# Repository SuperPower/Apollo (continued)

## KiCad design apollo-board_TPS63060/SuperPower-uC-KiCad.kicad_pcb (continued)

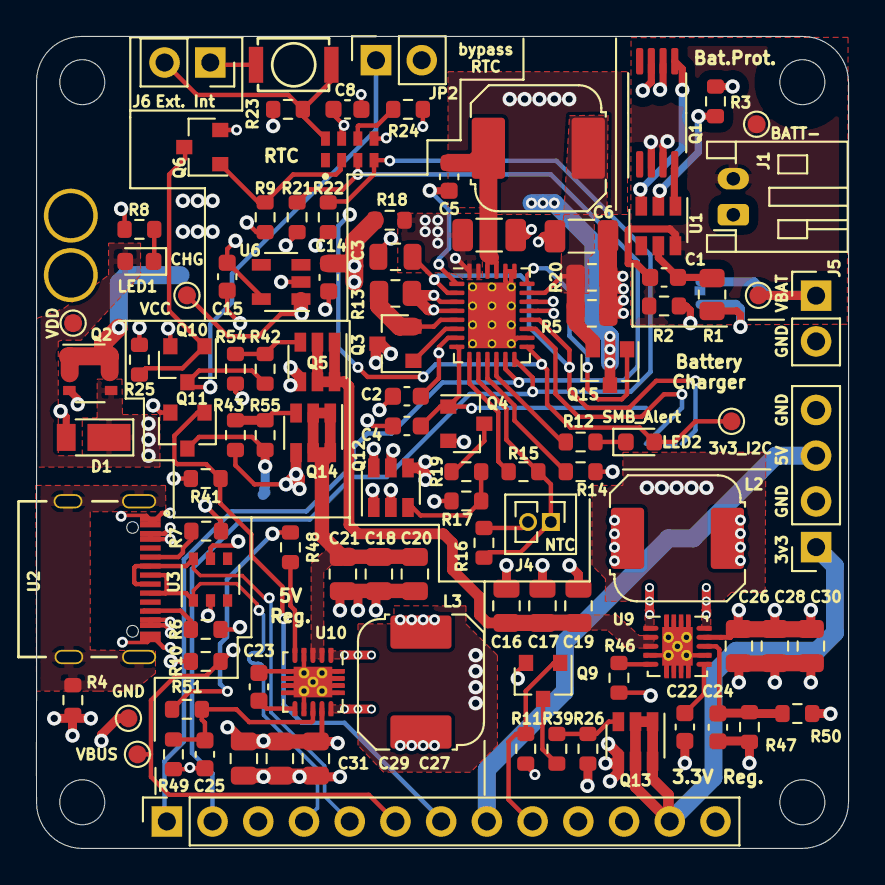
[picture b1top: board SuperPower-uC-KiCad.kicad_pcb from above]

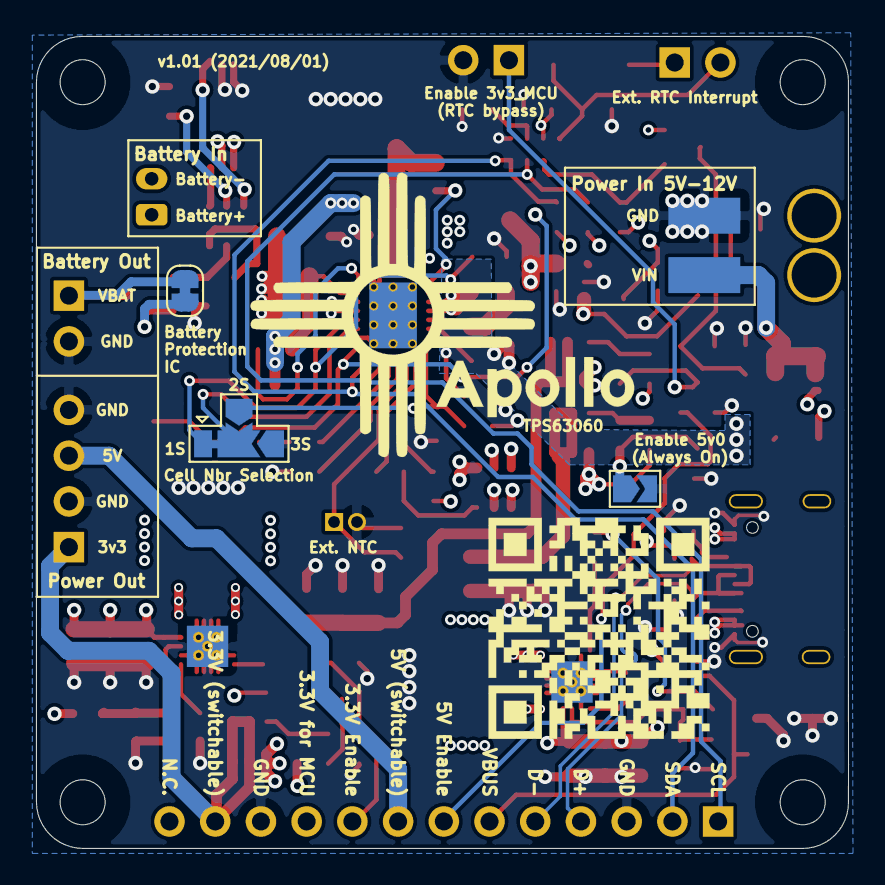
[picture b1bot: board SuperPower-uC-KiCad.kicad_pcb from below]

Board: 4 copper layers, 45.1 x 45.1 mm, 114 parts (4 on the bottom side), 65 nets.

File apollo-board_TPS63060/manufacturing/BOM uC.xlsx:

Item | Qty | Reference(s) | Value | Footprint | Datasheet | Package | DNP
1 | 2 | C1, C2 | CC0603JRX7R9BB104 | Capacitor_SMD:C_0603_1608Metric | https://www.yageo.com/upload/media/product/productsearch/dat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 | 0603
2 | 1 | C3 | TMK212AB7475KG-T | Capacitor_SMD:C_0805_2012Metric | https://eu.mouser.com/datasheet/2/396/mlcc02_e-1307760.pdf | 0805
3 | 1 | C4 | CL10B105KO8NNNC | Capacitor_SMD:C_0603_1608Metric |  | 0603
4 | 1 | C5 | CL10B223KB8NNNC | Capacitor_SMD:C_0603_1608Metric |  | 0603
5 | 2 | C6, C7 | CL31B106KAHNNNE | Capacitor_SMD:C_1206_3216Metric | https://eu.mouser.com/datasheet/2/585/MLCC-1837944.pdf | 1206
6 | 1 | C8 | 0.1µF | Capacitor_SMD:C_0603_1608Metric | ~ | 0603
7 | 2 | C14, C15 | 2.2μF | Capacitor_SMD:C_0603_1608Metric | ~ | 0603
8 | 6 | C16, C17, C18, C19, C20, C21 | CL21A106KAYNNNE | Capacitor_SMD:C_0805_2012Metric | https://www.mouser.fr/datasheet/2/585/MLCC-1837944.pdf | 0805
9 | 2 | C22, C23 | CL10B104KB8NNNC | Capacitor_SMD:C_0603_1608Metric | https://www.mouser.fr/datasheet/2/585/MLCC-1837944.pdf | 0603
10 | 2 | C24, C25 | CC0603JRNPO9BN100 | Capacitor_SMD:C_0603_1608Metric | https://www.mouser.fr/datasheet/2/447/yageo_yago_s_a00092516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 | 0603
11 | 6 | C26, C27, C28, C29, C30, C31 | CL21A226MAQNNNE | Capacitor_SMD:C_0805_2012Metric | https://www.mouser.fr/datasheet/2/585/MLCC-1837944.pdf | 0805
12 | 1 | D1 | DFLS230L | Diode_SMD:D_PowerDI-123 | https://www.diodes.com/assets/Datasheets/ds30515.pdf | PowerDI-123-2
13 | 4 | H1, H2, H3, H4 | MountingHole | MountingHole:MountingHole_2.5mm | ~ |  | DNP
14 | 1 | J1 | JST_PH_S2B_thru | Connector_JST:JST_PH_S2B-PH-K_1x02_P2.00mm_Horizontal | http://www.jst-mfg.com/product/pdf/eng/ePH.pdf | PH Right Angle Thru 2pins
15 | 1 | J3 | Conn_01x02_Male | ext_input:ext_input_pads | ~ |  | DNP
16 | 1 | J4 | DNP/JST_ZH_S2B_thru | Connector_PinHeader_1.27mm:PinHeader_1x02_P1.27mm_Vertical | http://www.jst-mfg.com/product/pdf/eng/eZH.pdf | ZH Right Angle Thru 2pins | DNP
17 | 1 | J5 | DNP/JST_XH_S2B_thru | Connector_PinHeader_2.54mm:PinHeader_1x02_P2.54mm_Vertical | http://www.jst-mfg.com/product/pdf/eng/eXH.pdf | XH Right Angle Thru 2pins | DNP
18 | 1 | J6 | Conn_01x02_Male | Connector_PinSocket_2.54mm:PinSocket_1x02_P2.54mm_Vertical | ~ |  | DNP
19 | 1 | J10 | Conn_01x13_Male | Connector_PinSocket_2.54mm:PinSocket_1x13_P2.54mm_Vertical | ~ |  | DNP
20 | 1 | J11 | Conn_01x04_Male | Connector_PinSocket_2.54mm:PinSocket_1x04_P2.54mm_Vertical | ~ |  | DNP
21 | 1 | JP1 | SolderJumper_4_Bridged_1C | SOLDERJUMPER_4_BRIDGED_1C:SolderJumper-4_P2.0mm_Bridged1C_TrianglePad1.0x1.5mm_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 | ~ |  | DNP
22 | 1 | JP2 | Jumper_NC_Small | Connector_PinSocket_2.54mm:PinSocket_1x02_P2.54mm_Vertical | ~ |  | DNP
23 | 1 | JP3 | Jumper_NC_Small | Jumper:SolderJumper-2_P1.3mm_Open_TrianglePad1.0x1.5mm | ~ |  | DNP
24 | 1 | L1 | SPM6530T-4R7M | SPM6530T-4R7M:L_TDK_SPM6530T | https://product.tdk.com/info/en/catalog/datasheets/inductor_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 | 6,5x7,1x3,0mm
25 | 2 | L2, L3 | SPM6530T-1R5M | SPM6530T-1R5M:L_TDK_SPM6530T | https://product.tdk.com/info/en/catalog/datasheets/inductor_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 | 6,5x7,1x3,0mm
26 | 1 | LED1 | 150060VS75000_0603 | LED_SMD:LED_0603_1608Metric | https://www.we-online.com/catalog/datasheet/150060VS75000.pdf | 0603
27 | 1 | LED2 | 150060YS75000_0603 | LED_SMD:LED_0603_1608Metric | https://www.we-online.com/catalog/datasheet/150060YS75000.pdf | 0603 | DNP
28 | 1 | Q1 | DMN2019UTS | Package_SO:TSSOP-8_4.4x3mm_P0.65mm | https://www.diodes.com/assets/Datasheets/DMN2019UTS.pdf | TSSOP-8
29 | 1 | Q2 | Si3421DV | Package_SO:TSOP-6_1.65x3.05mm_P0.95mm | https://www.diodes.com/assets/Datasheets/DMP2035UVT.pdf | TSOP6
30 | 2 | Q3, Q15 | DMN3023L | Package_TO_SOT_SMD:SOT-23 | ~
31 | 4 | Q4, Q9, Q10, Q11 | 2N7002A | Package_TO_SOT_SMD:SOT-23 | https://www.diodes.com/assets/Datasheets/ds31360.pdf | SOT23-3
32 | 4 | Q5, Q12, Q13, Q14 | DMP2035UVT | Package_TO_SOT_SMD:SOT-23-6 | https://www.diodes.com/assets/Datasheets/DMP2035UVT.pdf | TSOT26
33 | 1 | Q6 | BSS84-7-F | Package_TO_SOT_SMD:SOT-23 | https://www.diodes.com/assets/Datasheets/ds30149.pdf | SOT23-3
34 | 1 | R1 | ERJ-P06F4700V | Resistor_SMD:R_0805_2012Metric | https://industrial.panasonic.com/cdbs/www-data/pdf/RDO0000/A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 | 0805
35 | 2 | R2, R18 | DNP/0 | Resistor_SMD:R_0603_1608Metric | ~ | 0603 | DNP
36 | 1 | R3 | 2.7k | Resistor_SMD:R_0603_1608Metric | ~ | 0603
37 | 1 | R4 | DNP/0 | Resistor_SMD:R_0603_1608Metric | ~ | 0603 | DNP
38 | 2 | R6, R7 | 5.1k | Resistor_SMD:R_0603_1608Metric | ~ | 0603
39 | 1 | R8 | 2.2k | Resistor_SMD:R_0603_1608Metric | ~ | 0603
40 | 4 | R9, R39, R54, R55 | 390k | Resistor_SMD:R_0603_1608Metric | ~ | 0603
41 | 1 | R10 | 12k | Resistor_SMD:R_0603_1608Metric | ~ | 0603
42 | 9 | R11, R25, R26, R41, R42, R43, R46, R48, R51 | 1M | Resistor_SMD:R_0603_1608Metric | ~ | 0603
43 | 1 | R12 | 2.2k | Resistor_SMD:R_0603_1608Metric | ~ | 0603 | DNP
44 | 2 | R13, R20 | RL0805FR-7W0R068L | Resistor_SMD:R_0805_2012Metric | https://www.yageo.com/upload/media/product/productsearch/dat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 | 0805
45 | 1 | R14 | 63.4k | Resistor_SMD:R_0603_1608Metric | ~ | 0603
46 | 2 | R15, R16 | 10k | Resistor_SMD:R_0603_1608Metric | ~ | 0603
47 | 1 | R17 | 1M | Resistor_SMD:R_0603_1608Metric | ~ | 0603
48 | 1 | R19 | 390k | Resistor_SMD:R_0603_1608Metric | ~ | 0603
49 | 2 | R21, R22 | 4.7k | Resistor_SMD:R_0603_1608Metric | ~ | 0603
50 | 1 | R23 | 100k | Resistor_SMD:R_0603_1608Metric | ~ | 0603
51 | 1 | R24 | 10k | Resistor_SMD:R_0603_1608Metric | ~ | 0603
52 | 1 | R47 | 100k | Resistor_SMD:R_0603_1608Metric | ~ | 0603
53 | 1 | R49 | 110k | Resistor_SMD:R_0603_1608Metric | ~ | 0603
54 | 1 | R50 | 560k | Resistor_SMD:R_0603_1608Metric | ~ | 0603
55 | 1 | SW1 | SKRKAEE020 | SKRKAEE020:SKRKAEE020
56 | 1 | U1 | AP9101CK6-AYTRG1 | Package_TO_SOT_SMD:SOT-23-6 | https://www.diodes.com/assets/Datasheets/AP9101C.pdf | SOT23-6
57 | 1 | U2 | USB-C | usb_c:usb-c-usb4105 | https://gct.co/files/drawings/usb4105.pdf
58 | 1 | U3 | IP4220CZ6 | Package_SO:TSOP-6_1.65x3.05mm_P0.95mm | https://assets.nexperia.com/documents/data-sheet/IP4220CZ6.pdf
59 | 1 | U4 | LTC4162EUFD-LAD | Package_DFN_QFN:QFN-28-1EP_4x5mm_P0.5mm_EP2.65x3.65mm_ThermalVias | https://www.analog.com/media/en/technical-documentation/data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 | QFN-28 (2.65x3.65mm)
60 | 1 | U5 | RV-3028-C7 | RV-3028-C7:IC_RV-3028-C7 | https://www.microcrystal.com/fileadmin/Media/Products/RTC/Da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
61 | 1 | U8 | TPS70933DRVT | Package_TO_SOT_SMD:SOT-23-6 | https://www.ti.com/lit/gpn/tps709
62 | 2 | U9, U10 | TPS63060 | TPS63060:Texas_S-PWSON-N10_ThermalVias_NSM_vias_bottom | http://www.ti.com/lit/ds/symlink/tps63060.pdf

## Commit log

2021-02-21 Move Repo and reduce project files to only contain the Apollo Board
2021-02-22 Replace TPS63070 by TPS63060 (U9)
    - Schematic Only
    - Update Netlist
    Rem. : 18650 bat. holder + DC Power Jack + TP (x7) are added while update from schematic process.
2021-02-22 Remove unused parts at schematic level.
    + solve schematic DRC issues
2021-02-22 Place and route U9 (TPS63060)
    + re-place other parts
    + re-design planes shapes
    + display some silkscreen Ref. Des
    + misc. improvements.
2021-02-23 Add TPS63060 component files
    + 3D package
2021-02-24 Update 22µF 0805 & 100nF 0603 capacitors
    around TPS63060
2021-02-24 Update 10µF 0805 capacitors
    Around TPS63060
2021-02-24 Update 10pF 0603 capacitor
    around TPS63060
2021-02-27 Place and route the 2nd TPS63060 (+5V)
2021-02-27 Update 22µF 0805 and 10pF 0603 capacitors
    + Silk Ref. Des.
2021-02-27 Update 10µF 0805 and 100nF 0603 capacitors
    + silk Ref. Des.
    Rem. : Apollo Logo and name on Silkscreen Bottom seem to be lost.
2021-02-28 Update +5V Buck-Boost Feedback resistor values
2021-02-28 Use a new footprint for TPS63060 chips
    Remove Bottom Soldermask on vias
2021-02-28 Improve USB Data diff. Pair length.
2021-02-28 Update Buck-Boost Feedback Resistor values
    - Use common values + bridge divider iq >3µA
    - Misc. Routing : increase one track width from 0.25 to 0.28mm (+5V Output)
2021-02-28 Update USB-C receptacle symbol fields
    Add Mfr Name & ref., DataSheet + Alternative Equivalent Part
2021-02-28 Re-Add "Apollo Logo" on Silkscreen bottom Layer
2021-02-28 Update "RTC Bypass" text position
    + Add "-A" extension pour TPS63060 variant
2021-03-01 Update Silkscreen board informations
    + Add a 12x12mm Text QR-Code
2021-03-03 Replace Text Data QR Code by Web Link QR Code
    https://superpower.github.io/docs/uc/prod/apv100/
2021-03-03 Replace QR-Code by 5x5mm size (x2)
    Web Link + Text Datas
2021-03-08 Generated manufacturing files (deleted wrong gerbers)
2021-03-09 Update TPS63060 chips footprint
    Removing "Solder Mask Openings" between EPad pins for each row
2021-03-09 Update QR-Code Web Link Size
    replace 5x5mm by 12x12mm
2021-04-06 Fixed PNP file
2021-06-13 Recreate TPS709 symbol to and set footprint to SOT23-5
2021-06-13 Connected VIN to I2C_REG
2021-06-13 Swapped Q3 and Q15 Symbol + Footprint
2021-06-13 Moved C3 closer to the LTC
2021-07-19 Remove SMBALERT wire
    between LTC4162-L chip (pin12) and the 2.54mm pitch 13pin connector (pin13). It will allow to use this pin for "one wire" RGB LED (RGB LED Out)
2021-07-19 Update SMBALERT LED (LED2) and resistor (R12) to DNP (Do Not Populate)
2021-07-19 Add a Solder Jumper (shorted by default) between Vbat+ and R1 (AP9101)
2021-07-19 Clean "Battery Protection IC" schematic
2021-07-19 Update "Main Schematic" text
2021-07-19 Update and clean "charger" sheet + add "Vcc" test point
2021-07-19 Rename some power signal on Schematic to improve readability.
    + Misc. updates
2021-07-19 Improve Power tracks width on Bottom Layer
2021-07-19 Improve Power Tracks width and Vias on Top Layer (+3.3V regulator)
2021-07-19 Improve PowerTracks width and Vias on Top Layer (+5.0V)
    + Flip JP3
2021-07-19 Improve Power Tracks width and Vias on Top Layer (+3.3V)
2021-07-19 Improve Tracks width and vias around LTC4162-L
2021-07-19 Improve Tracks width and Vias around LTC4162-L (Q3)
2021-07-19 Q15 Track width issue correction
2021-07-24 Flip JP1 Cell Number Selection (Top to bottom Layer)
    + Misc. Silkscreen updates
2021-07-24 Update Silkscreen Bottom
2021-07-24 Add 12x12mm QR Code (Web Link)
2021-07-24 Update Silkscreen Layer Top
2021-08-02 Add second 0805 resistor for Rsns (R20)
    - Add second 0805 resistor for Rsns (R20) and update values by 130 mOhm
    - Update Silkscreen layer (Ref Des. , text, etc.)
2021-08-02 Move Silkscreen Text from via (Bottom Layer)
2021-08-02 Move Silkscreen Text from via (Bottom Layer)
    + Highlight New DNP items on XLS BOM file
2021-08-03 Update 0805 resistor library link issue
2021-08-04 MArked logos as virtual footprints to remove them from the bom
2021-08-04 Created BOM
2021-08-04 Generated Gerber files incl. pos files and drilling
2021-08-05 Update LED2 value as DNP + Manually Update BOM
